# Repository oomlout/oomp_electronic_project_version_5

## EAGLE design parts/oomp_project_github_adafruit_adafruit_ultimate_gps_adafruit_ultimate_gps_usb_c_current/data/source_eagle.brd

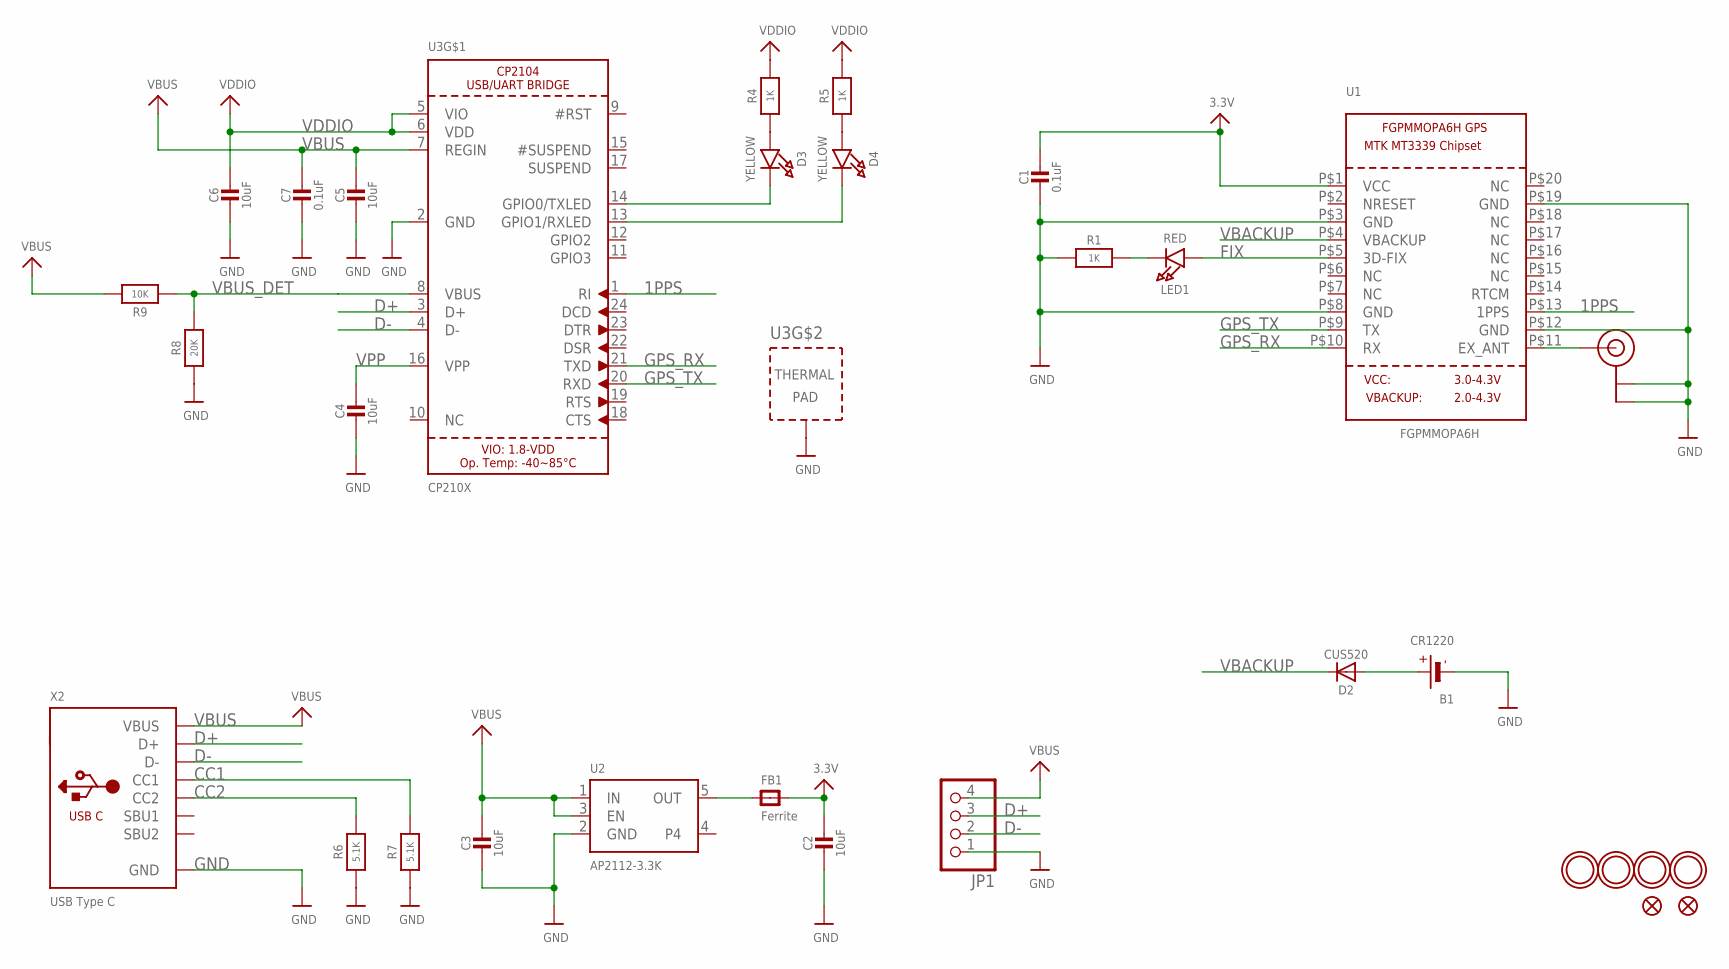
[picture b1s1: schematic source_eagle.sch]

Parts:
B1: CR1220
C1, C7: 0.1uF; 0603-NO
C2, C3, C4, C5, C6: 10uF; 0805-NO
D2: CUS520; SOD-323
D3, D4: YELLOW; CHIPLED_0805_NOOUTLINE
FB1: Ferrite; 0805-NO
FID1, FID2: FIDUCIAL_1MM
JP1: HEADER-1X4ROUND; 1X04_ROUND
LED1: RED; CHIPLED_0805_NOOUTLINE
R1, R4, R5: 1K; 0603-NO
R6, R7: 5.1K; 0603-NO
R8: 20K; 0603-NO
R9: 10K; 0603-NO
U1: FGPMMOPA6H
U2: AP2112-3.3K; SOT23-5
U3: CP210X; QFN24_4MM_SMSC
U$8, U$9, U$35, U$36: MOUNTINGHOLE2.5; MOUNTINGHOLE_2.5_PLATED
U$20: U.FL
X2: USB Type C; USB_C_CUSB31-CFM2AX-01-X

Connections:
1PPS: U1.P$13 (1PPS), U3.1 (RI)
3.3V: C1.1, C2.1, FB1.2, U1.P$1 (VCC)
CC1: R7.2, X2.A5 (CC1)
CC2: R6.2, X2.B5 (CC2)
D+: JP1.3, U3.3 (D+), X2.A6 (D+), X2.B6 (D+)
D-: JP1.2, U3.4 (D-), X2.A7 (D-), X2.B7 (D-)
FIX: LED1.A, U1.P$5 (3D-FIX)
GND: B1.-, C1.2, C2.2, C3.2, C4.2, C5.2, C6.2, C7.2, JP1.1, R1.1, R6.1, R7.1, R8.1, U1.P$3 (GND), U1.P$8 (GND), U1.P$12 (GND), U1.P$19 (GND), U2.2 (GND), U3.2 (GND), U3.THERM (TP), U$20.P$1 (GND), U$20.P$2 (GND), X2.A1B12 (GND), X2.B1A12 (GND)
GPS_RX: U1.P$10 (RX), U3.21 (TXD)
GPS_TX: U1.P$9 (TX), U3.20 (RXD)
unnamed: B1.+$1 (+), B1.+$2 (+), D2.A
unnamed: LED1.C, R1.2
unnamed: FB1.1, U2.5 (OUT)
unnamed: U1.P$11 (EX_ANT), U$20.P$3 (SIGNAL)
unnamed: D3.A, R4.1
unnamed: D4.A, R5.1
unnamed: D3.C, U3.14 (GPIO0/TXLED)
unnamed: D4.C, U3.13 (GPIO1/RXLED)
VBACKUP: D2.C, U1.P$4 (VBACKUP)
VBUS: C3.1, C5.1, C7.1, JP1.4, R9.2, U2.1 (IN), U2.3 (EN), U3.7 (REGIN), X2.A4B9 (VBUS), X2.B4A9 (VBUS)
VBUS_DET: R8.2, R9.1, U3.8 (VBUS)
VDDIO: C6.1, R4.2, R5.2, U3.5 (VIO), U3.6 (VDD)
VPP: C4.1, U3.16 (VPP)

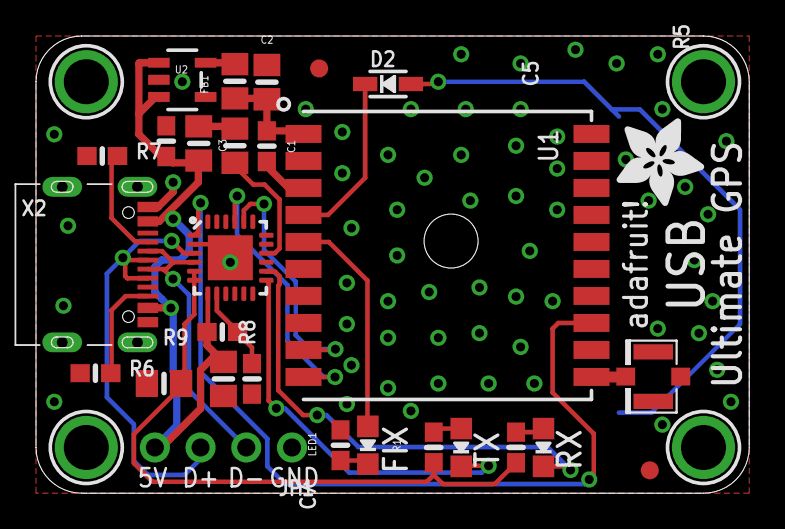
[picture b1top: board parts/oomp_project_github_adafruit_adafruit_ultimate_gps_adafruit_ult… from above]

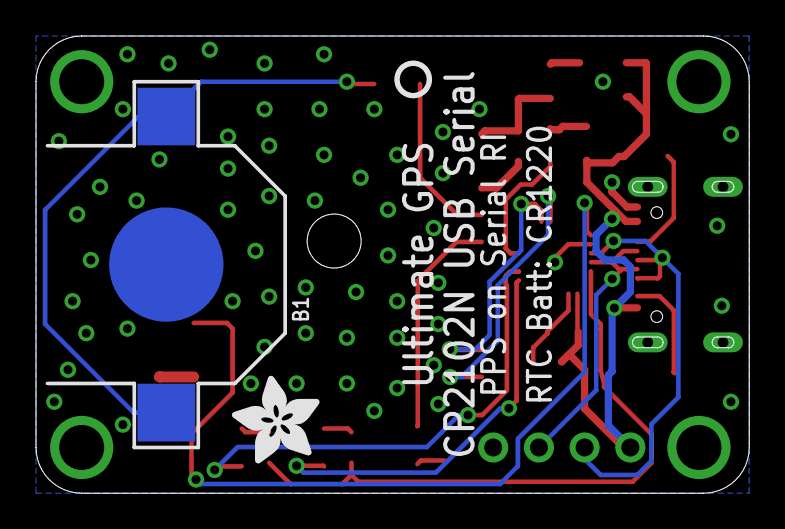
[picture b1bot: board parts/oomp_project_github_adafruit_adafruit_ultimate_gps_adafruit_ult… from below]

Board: 2 copper layers, 39.6 x 25.4 mm, 35 parts (3 on the bottom side), 23 nets.

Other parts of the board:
U$13, U$18: ADAFRUIT_5MM
U$16: PCBFEAT-REV-040

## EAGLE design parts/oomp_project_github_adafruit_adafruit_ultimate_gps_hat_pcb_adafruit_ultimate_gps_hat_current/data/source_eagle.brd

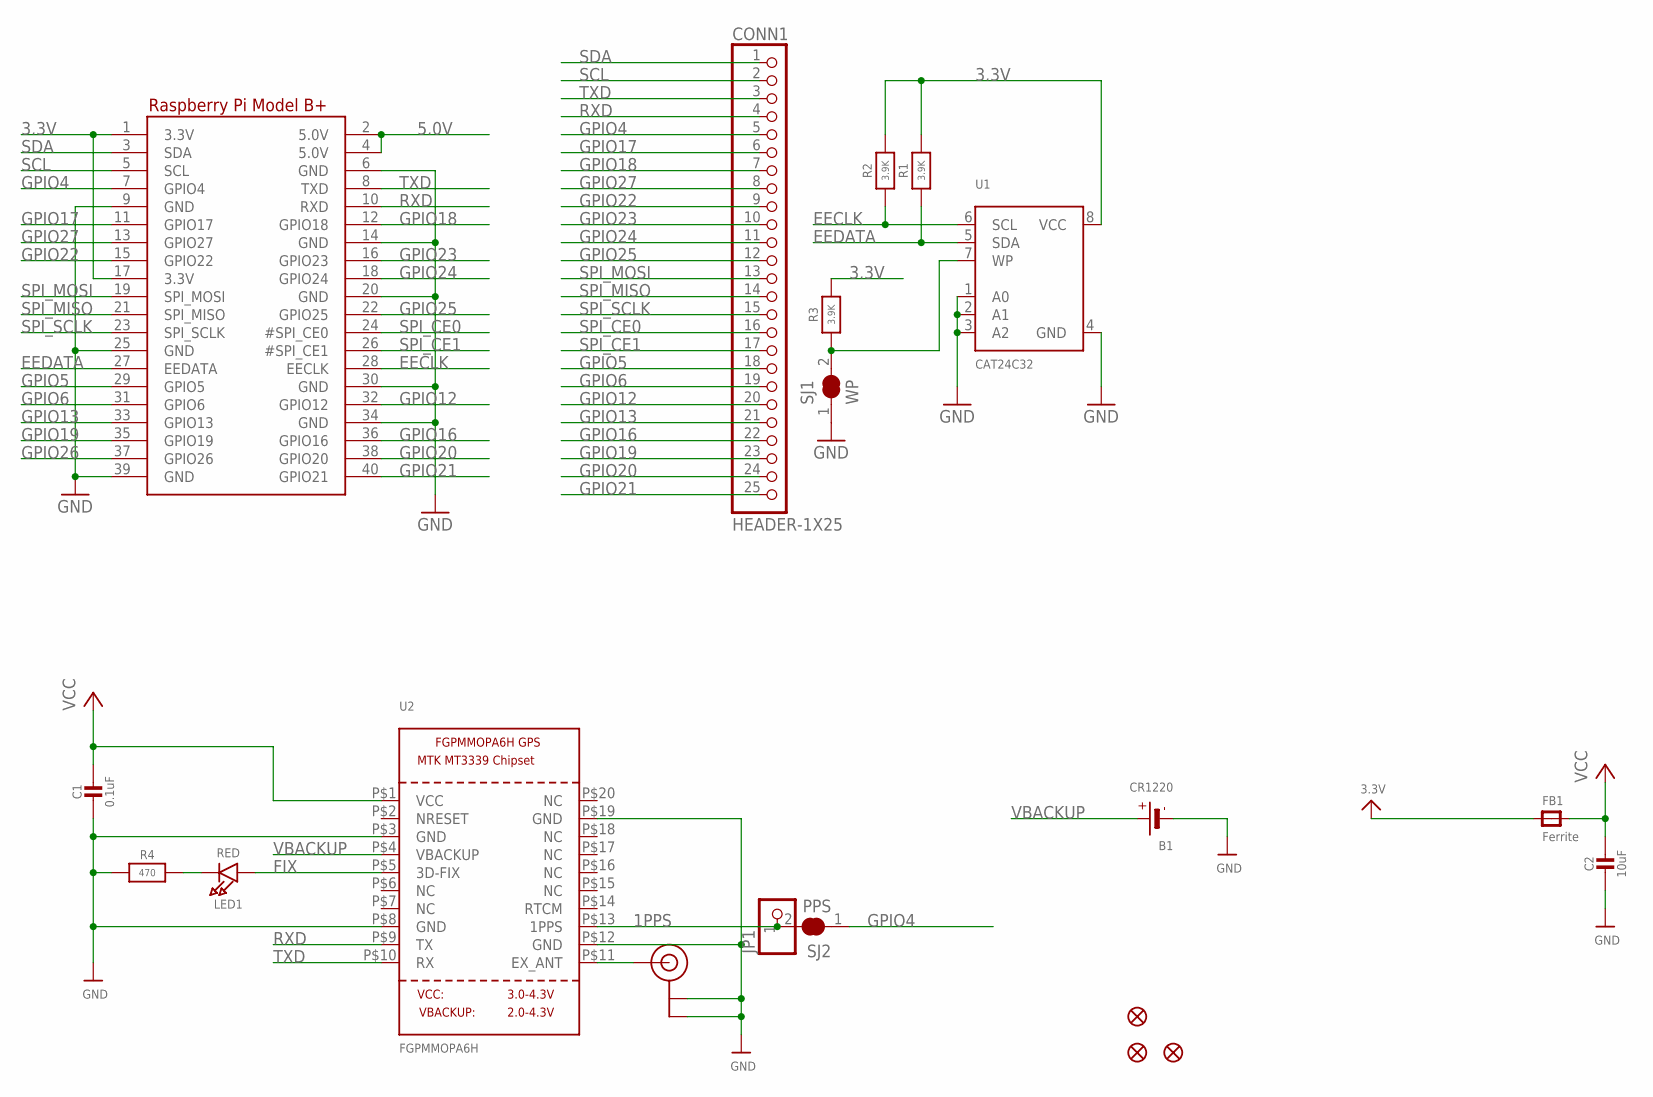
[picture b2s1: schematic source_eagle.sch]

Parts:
B1: CR1220
C1: 0.1uF; 0805-NO
C2: 10uF; 0805-NO
CONN1: HEADER-1X25; 1X25_ROUND_70MIL
FB1: Ferrite; 0805
FID1, FID2, FID3: FIDUCIAL""; FIDUCIAL_1MM
JP1: PINHD-1X1CB; 1X01-CLEANBIG
LED1: RED; CHIPLED_0805
R1, R2, R3: 3.9K; 0805-NO
R4: 470; 0805-NO
RPI1: RASPBERRYPI_BPLUS_HATSLOTS; PI_HAT_SLOTS
SJ1: WP; SOLDERJUMPER_CLOSEDWIRE
SJ2: PPS; SOLDERJUMPER_CLOSEDWIRE
U1: CAT24C32; SOIC8_150MIL
U2: FGPMMOPA6H
U$20: U.FL

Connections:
1PPS: JP1.1, SJ2.2, U2.P$13 (1PPS)
3.3V: FB1.1, R1.2, R2.2, R3.2, RPI1.1 (3.3V), RPI1.17 (3.3V), U1.8 (VCC)
5.0V: RPI1.2 (5.0V), RPI1.4 (5.0V)
EECLK: R2.1, RPI1.28 (EECLK), U1.6 (SCL)
EEDATA: R1.1, RPI1.27 (EEDATA), U1.5 (SDA)
FIX: LED1.A, U2.P$5 (3D-FIX)
GND: B1.-, C1.2, C2.2, R4.1, RPI1.6 (GND), RPI1.9 (GND), RPI1.14 (GND), RPI1.20 (GND), RPI1.25 (GND), RPI1.30 (GND), RPI1.34 (GND), RPI1.39 (GND), SJ1.1, U1.1 (A0), U1.2 (A1), U1.3 (A2), U1.4 (GND), U2.P$3 (GND), U2.P$8 (GND), U2.P$12 (GND), U2.P$19 (GND), U$20.P$1 (GND), U$20.P$2 (GND)
GPIO4: CONN1.5, RPI1.7 (GPIO4), SJ2.1
GPIO5: CONN1.18, RPI1.29 (GPIO5)
GPIO6: CONN1.19, RPI1.31 (GPIO6)
GPIO12: CONN1.20, RPI1.32 (GPIO12)
GPIO13: CONN1.21, RPI1.33 (GPIO13)
GPIO16: CONN1.22, RPI1.36 (GPIO16)
GPIO17: CONN1.6, RPI1.11 (GPIO17)
GPIO18: CONN1.7, RPI1.12 (GPIO18)
GPIO19: CONN1.23, RPI1.35 (GPIO19)
GPIO20: CONN1.24, RPI1.38 (GPIO20)
GPIO21: CONN1.25, RPI1.40 (GPIO21)
GPIO22: CONN1.9, RPI1.15 (GPIO22)
GPIO23: CONN1.10, RPI1.16 (GPIO23)
GPIO24: CONN1.11, RPI1.18 (GPIO24)
GPIO25: CONN1.12, RPI1.22 (GPIO25)
GPIO26: RPI1.37 (GPIO26)
GPIO27: CONN1.8, RPI1.13 (GPIO27)
unnamed: R3.1, SJ1.2, U1.7 (WP)
unnamed: LED1.C, R4.2
unnamed: U2.P$11 (EX_ANT), U$20.P$3 (SIGNAL)
RXD: CONN1.4, RPI1.10 (RXD), U2.P$9 (TX)
SCL: CONN1.2, RPI1.5 (SCL)
SDA: CONN1.1, RPI1.3 (SDA)
SPI_CE0: CONN1.16, RPI1.24 (#SPI_CE0)
SPI_CE1: CONN1.17, RPI1.26 (#SPI_CE1)
SPI_MISO: CONN1.14, RPI1.21 (SPI_MISO)
SPI_MOSI: CONN1.13, RPI1.19 (SPI_MOSI)
SPI_SCLK: CONN1.15, RPI1.23 (SPI_SCLK)
TXD: CONN1.3, RPI1.8 (TXD), U2.P$10 (RX)
VBACKUP: B1.+$1 (+), U2.P$4 (VBACKUP)
VCC: C1.1, C2.1, FB1.2, U2.P$1 (VCC)

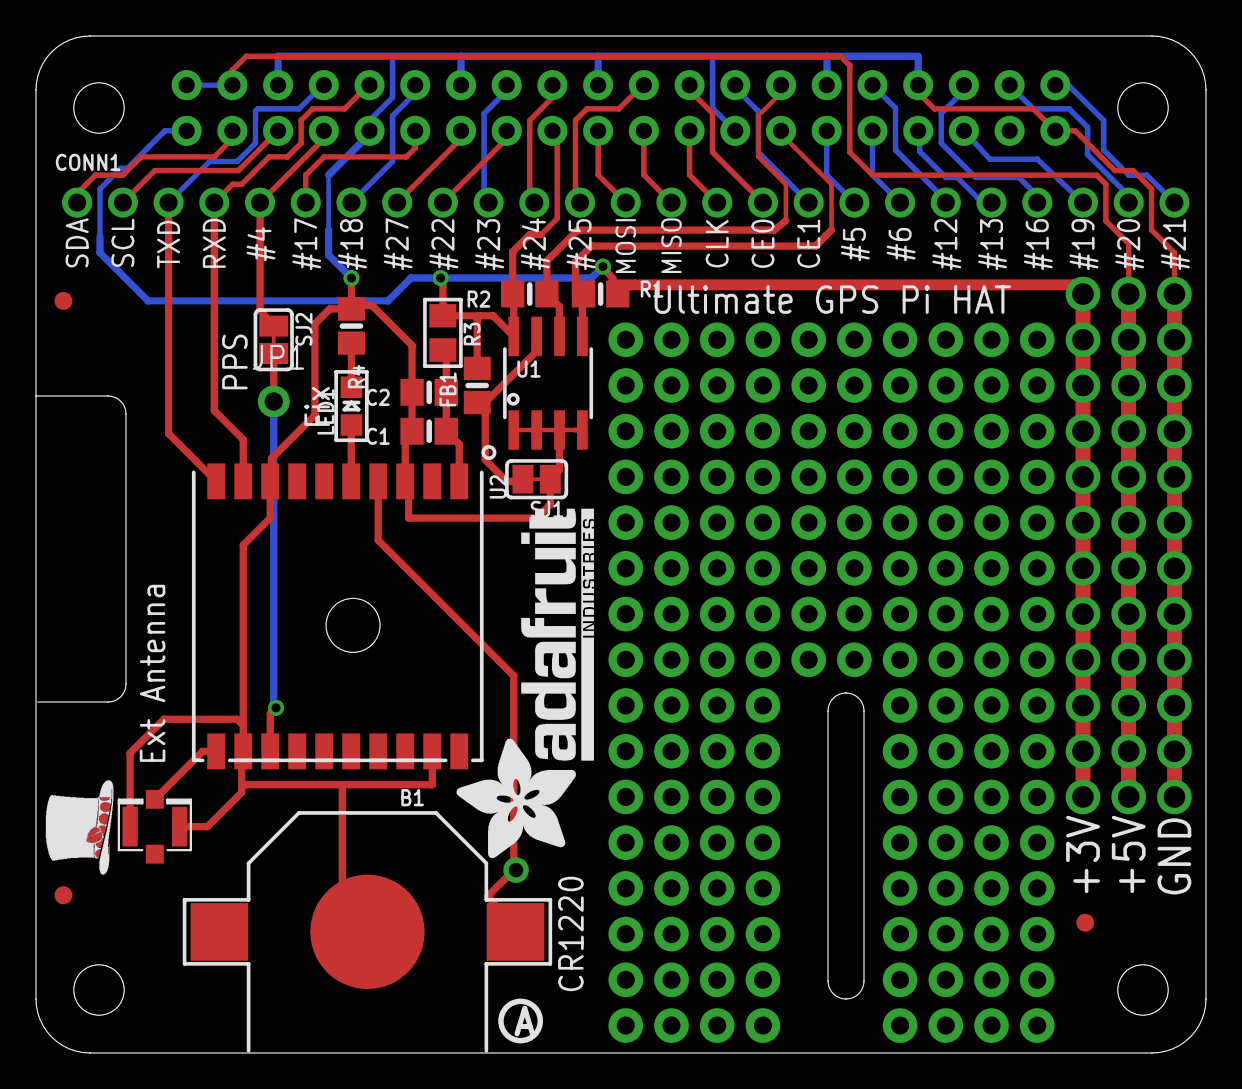
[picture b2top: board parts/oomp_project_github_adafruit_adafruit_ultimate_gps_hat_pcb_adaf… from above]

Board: 2 copper layers, 65.0 x 56.5 mm, 23 parts (0 on the bottom side), 37 nets.

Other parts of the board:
U$3: ADAFRUIT_TEXT_20MM
U$4: PIHATLOGO
U$6: PCBFEAT-REV-056

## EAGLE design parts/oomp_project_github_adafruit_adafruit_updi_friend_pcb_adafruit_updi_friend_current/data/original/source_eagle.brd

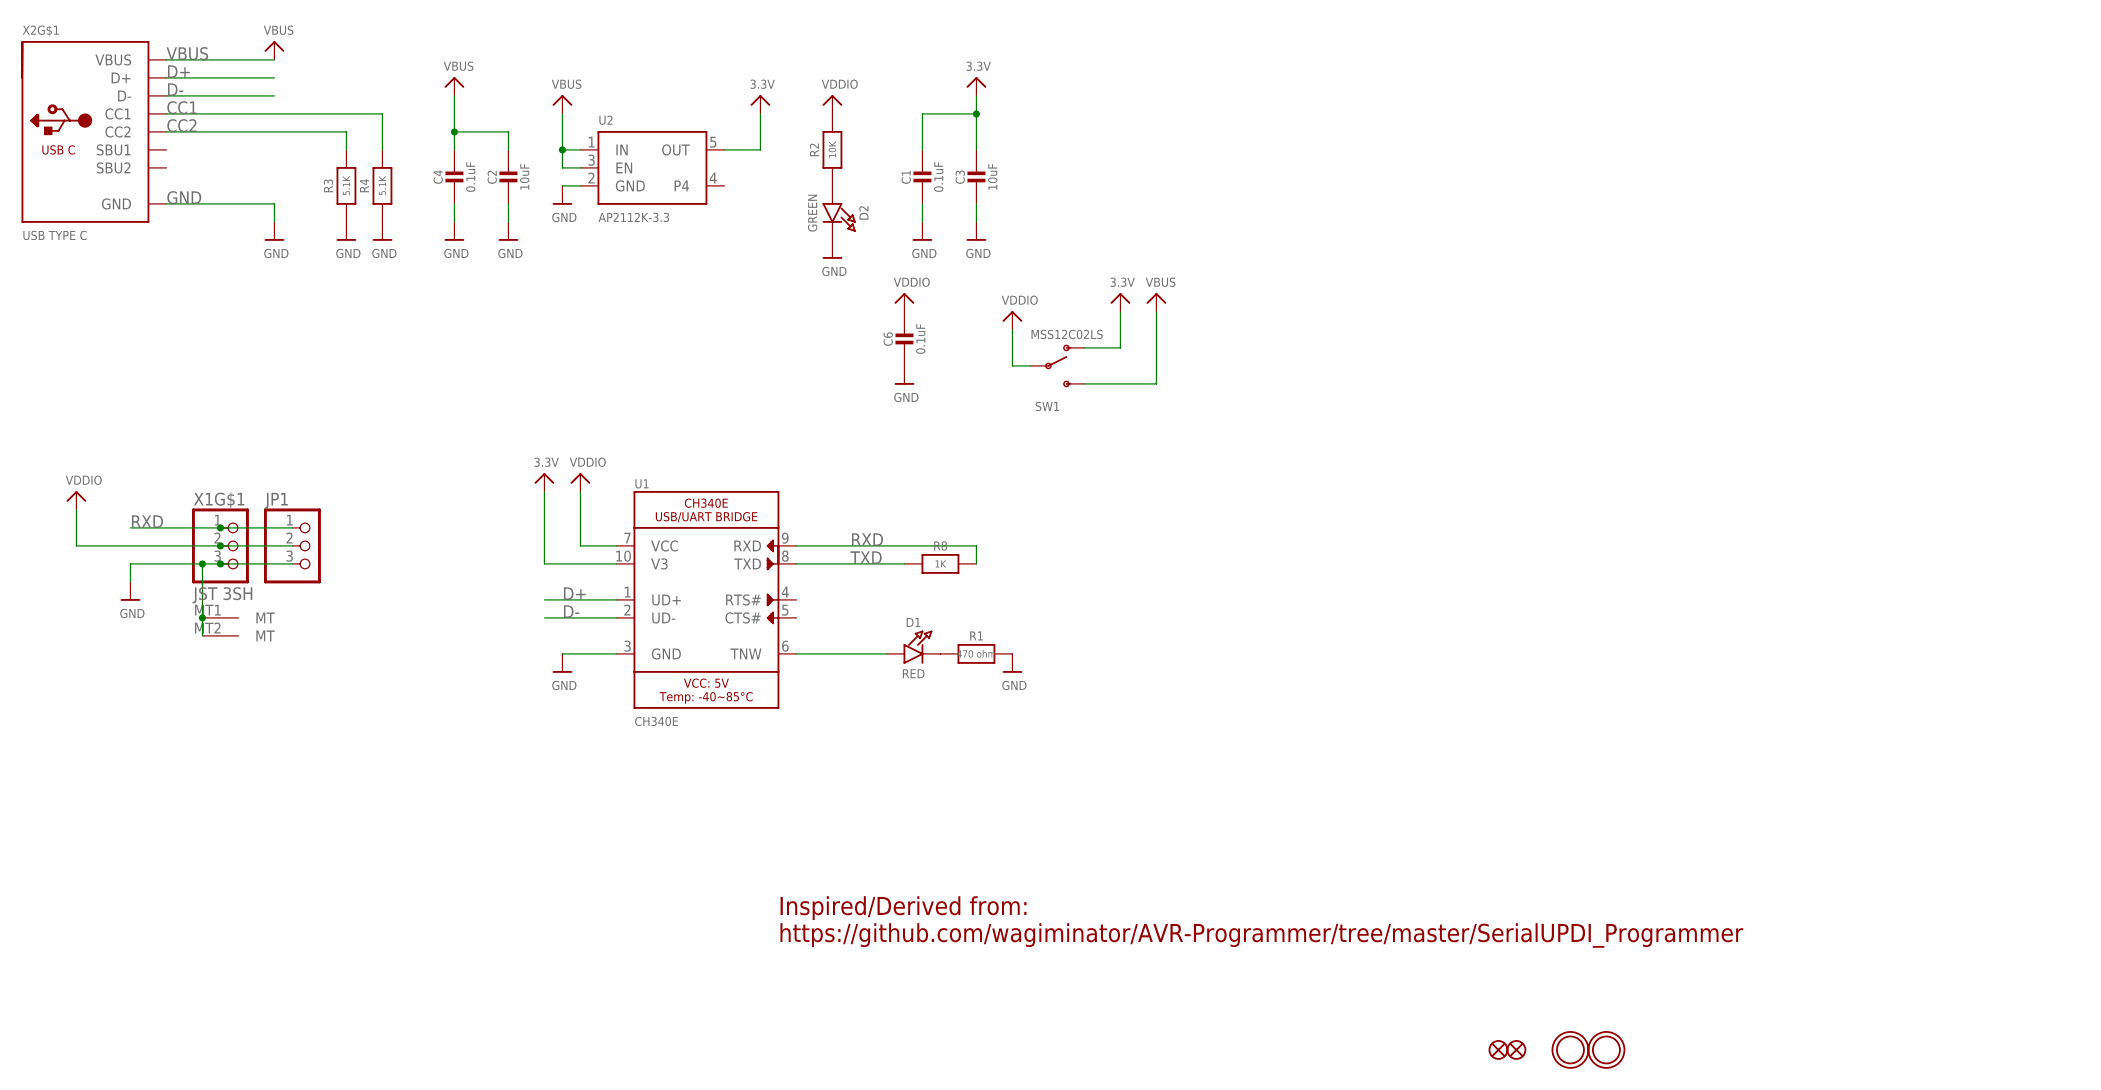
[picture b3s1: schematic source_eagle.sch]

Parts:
C1, C4, C6: 0.1uF; 0603-NO
C2, C3: 10uF; 0805-NO
D1: RED; CHIPLED_0603_NOOUTLINE
D2: GREEN; CHIPLED_0603_NOOUTLINE
FID1, FID2: FIDUCIAL_1MM
JP1: HEADER-1X376MIL; 1X03_ROUND_76
R1: 470 ohm; 0603-NO
R2: 10K; 0603-NO
R3, R4: 5.1K; 0603-NO
R8: 1K; 0603-NO
SW1: MSS12C02LS; SPDT_SMT_SSSS811101
U1: CH340E; MSOP10
U2: AP2112K-3.3; SOT23-5; JLC_ROTATION 0
U$18, U$19: MOUNTINGHOLE2.0; MOUNTINGHOLE_2.0_PLATED
X1: JST 3SH; JST_SH3
X2: USB TYPE C; USB_C_CUSB31-CFM2AX-01-X

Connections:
3.3V: C1.1, C3.1, SW1.A (O), U1.10 (V3), U2.5 (OUT)
CC1: R4.2, X2.A5 (CC1)
CC2: R3.2, X2.B5 (CC2)
D+: U1.1 (UD+), X2.A6 (D+), X2.B6 (D+)
D-: U1.2 (UD-), X2.A7 (D-), X2.B7 (D-)
GND: C1.2, C2.2, C3.2, C4.2, C6.2, D2.C, JP1.3, R1.2, R3.1, R4.1, U1.3 (GND), U2.2 (GND), X1.3, X1.MT1 (MT), X1.MT2 (MT), X2.A1B12 (GND), X2.B1A12 (GND)
unnamed: D1.C, R1.1
unnamed: D1.A, U1.6 (TNW)
unnamed: D2.A, R2.1
RXD: JP1.1, R8.2, U1.9 (RXD), X1.1
TXD: R8.1, U1.8 (TXD)
VBUS: C2.1, C4.1, SW1.C (S), U2.1 (IN), U2.3 (EN), X2.A4B9 (VBUS), X2.B4A9 (VBUS)
VDDIO: C6.1, JP1.2, R2.2, SW1.B, U1.7 (VCC), X1.2

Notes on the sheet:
Inspired/Derived from: https://github.com/wagiminator/AVR-Programmer/tree/master/SerialUPDI_Programmer

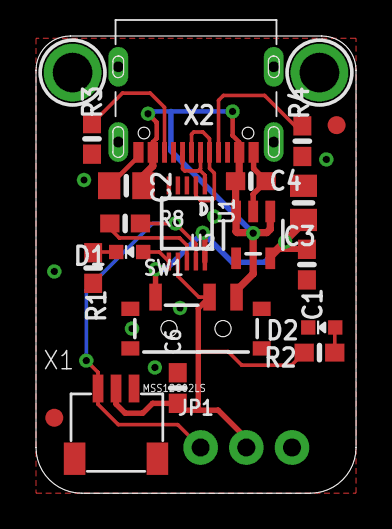
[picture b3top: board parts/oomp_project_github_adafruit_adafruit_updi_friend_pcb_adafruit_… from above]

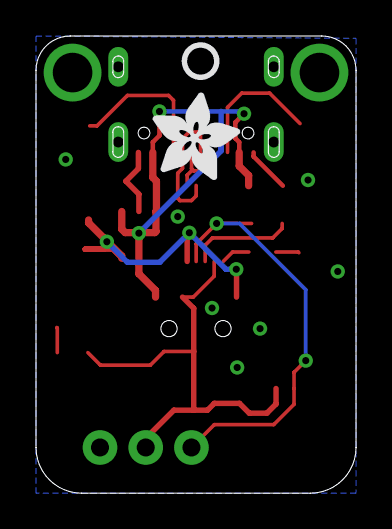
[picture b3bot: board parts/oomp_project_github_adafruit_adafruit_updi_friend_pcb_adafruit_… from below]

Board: 2 copper layers, 17.8 x 25.4 mm, 37 parts (7 on the bottom side), 13 nets.

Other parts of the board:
PLABEL0: PLABEL0
PLABEL1: PLABEL1
PLABEL2: PLABEL2
PLABEL3: PLABEL3
PLABEL4: PLABEL4
PLABEL5: PLABEL5
PLABEL6: PLABEL6
PLABEL7: PLABEL7
PLABEL8: PLABEL8
PLABEL9: PLABEL9
PLABEL10: PLABEL10
PLABEL11: PLABEL11
PLABEL12: PLABEL12
U$9: ADAFRUIT_5MM
U$17: PCBFEAT-REV-040

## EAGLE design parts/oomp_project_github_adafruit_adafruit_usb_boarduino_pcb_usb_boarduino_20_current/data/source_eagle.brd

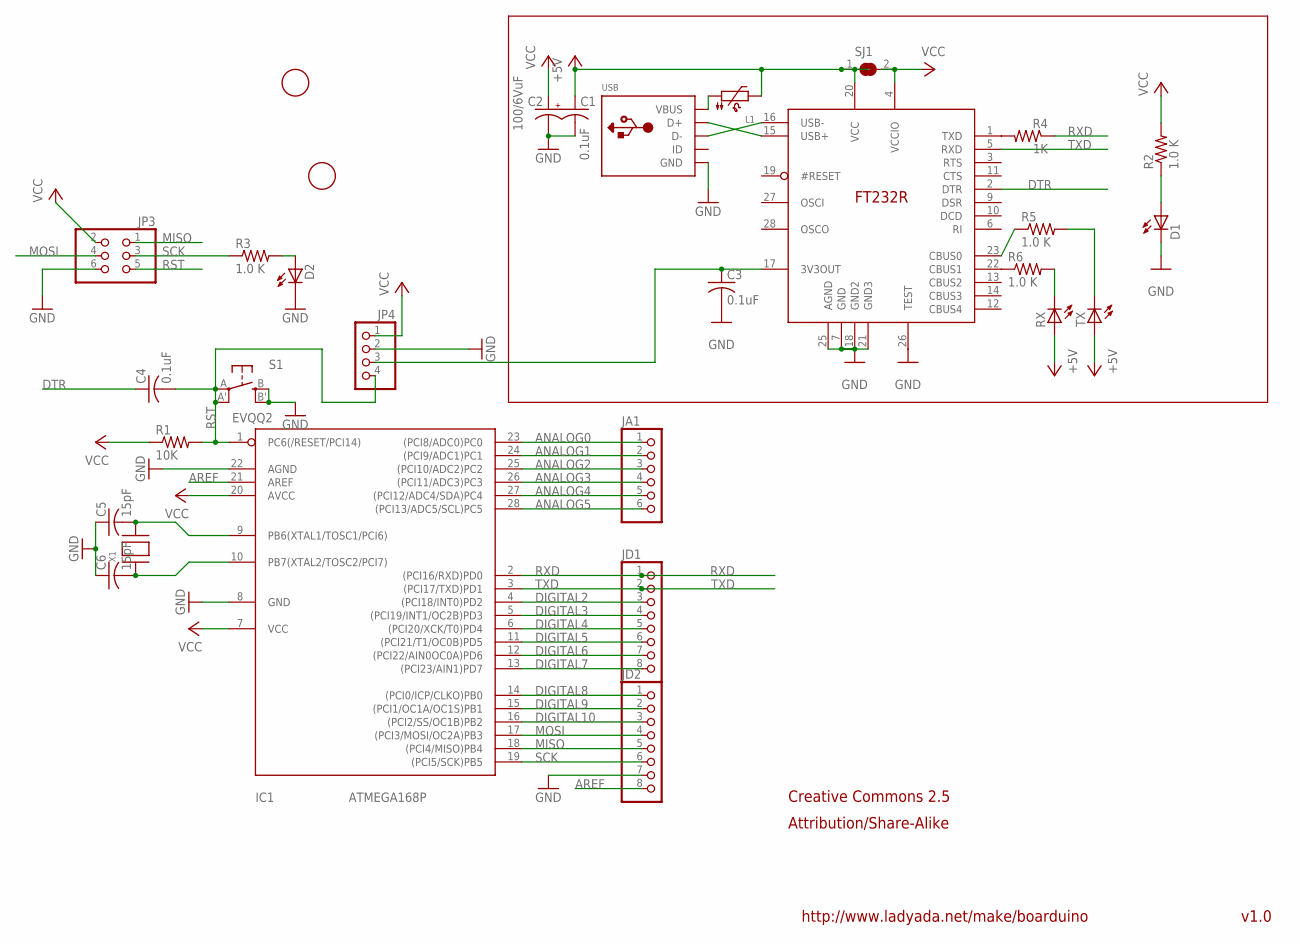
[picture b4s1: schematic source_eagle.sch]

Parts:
C1, C3, C4: 0.1uF; C0805K
C2: 100/6VuF; B/3528-21R
C5, C6: 15pF; C0805K
D1: LEDCHIPLED_0805; CHIPLED_0805
D2: Green; CHIPLED_0805
IC1: ATMEGA168P; DIL28/3
IC2: FT232R; TSSOP28
JA1: PINHD-1X6CB; 1X06-CLEANBIG
JD1, JD2: PINHD-1X8CLEANBIG; 1X08-CLEANBIG
JP3: PINHD-2X3; 2X03
JP4: PINHD-1X4CB; 1X04-CB
L1: PTC1206; 1206
R1: 10K; R0805
R2, R3, R5, R6: 1.0 K; R0805
R4: 1K; R0805
RX: Green; CHIPLED_0805
S1: EVQQ2; EVQ-Q2
SJ1: SOLDERJUMPERREFLOW; SOLDERJUMPER_REFLOW
TX: Green; CHIPLED_0805
U$1, U$2: FIDUCIAL; FIDUCIAL_1MM
USB: USBMINIB; USB-MINIB
X1: XTALNX5032; NX5032

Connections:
3V: C3.1, IC2.17 (3V3OUT), JP4.3
+5V: C1.1, IC2.20 (VCC), L1.2, RX.A, SJ1.1, TX.A
ANALOG0: IC1.23 ((PCI8/ADC0)PC0), JA1.1
ANALOG1: IC1.24 ((PCI9/ADC1)PC1), JA1.2
ANALOG2: IC1.25 ((PCI10/ADC2)PC2), JA1.3
ANALOG3: IC1.26 ((PCI11/ADC3)PC3), JA1.4
ANALOG4: IC1.27 ((PCI12/ADC4/SDA)PC4), JA1.5
ANALOG5: IC1.28 ((PCI13/ADC5/SCL)PC5), JA1.6
AREF: IC1.21 (AREF), JD2.8
DIGITAL2: IC1.4 ((PCI18/INT0)PD2), JD1.3
DIGITAL3: IC1.5 ((PCI19/INT1/OC2B)PD3), JD1.4
DIGITAL4: IC1.6 ((PCI20/XCK/T0)PD4), JD1.5
DIGITAL5: IC1.11 ((PCI21/T1/OC0B)PD5), JD1.6
DIGITAL6: IC1.12 ((PCI22/AIN0OC0A)PD6), JD1.7
DIGITAL7: IC1.13 ((PCI23/AIN1)PD7), JD1.8
DIGITAL8: IC1.14 ((PCI0/ICP/CLKO)PB0), JD2.1
DIGITAL9: IC1.15 ((PCI1/OC1A/OC1S)PB1), JD2.2
DIGITAL10: IC1.16 ((PCI2/SS/OC1B)PB2), JD2.3
DTR: C4.1, IC2.2 (DTR)
GND: C1.2, C2.-, C3.2, C5.1, C6.1, D1.C, D2.C, IC1.8 (GND), IC1.22 (AGND), IC2.7 (GND), IC2.18 (GND2), IC2.21 (GND3), IC2.25 (AGND), IC2.26 (TEST), JD2.7, JP3.6, JP4.2, S1.B (S), S1.B' (S1), USB.GND
MISO: IC1.18 ((PCI4/MISO)PB4), JD2.5, JP3.1
MOSI: IC1.17 ((PCI3/MOSI/OC2A)PB3), JD2.4, JP3.4
unnamed: C5.2, IC1.9 (PB6(XTAL1/TOSC1/PCI6)), X1.P$2
unnamed: C6.2, IC1.10 (PB7(XTAL2/TOSC2/PCI7)), X1.P$1
unnamed: D1.A, R2.1
unnamed: D2.A, R3.2
unnamed: IC2.15 (USB+), USB.D+
unnamed: IC2.16 (USB-), USB.D-
unnamed: IC2.1 (TXD), R4.2
unnamed: L1.1, USB.VBUS
unnamed: R6.2, RX.C
unnamed: R5.2, TX.C
unnamed: IC2.22 (CBUS1), R6.1
unnamed: IC2.23 (CBUS0), R5.1
RST: C4.2, IC1.1 (PC6(/RESET/PCI14)), JP3.5, JP4.4, R1.2, S1.A, S1.A' (P1)
RXD: IC1.2 ((PCI16/RXD)PD0), JD1.1, R4.1
SCK: IC1.19 ((PCI5/SCK)PB5), JD2.6, JP3.3, R3.1
TXD: IC1.3 ((PCI17/TXD)PD1), IC2.5 (RXD), JD1.2
VCC: C2.+, IC1.7 (VCC), IC1.20 (AVCC), IC2.4 (VCCIO), JP3.2, JP4.1, R1.1, R2.2, SJ1.2

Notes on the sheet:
v1.0
http://www.ladyada.net/make/boarduino
Creative Commons 2.5
Attribution/Share-Alike

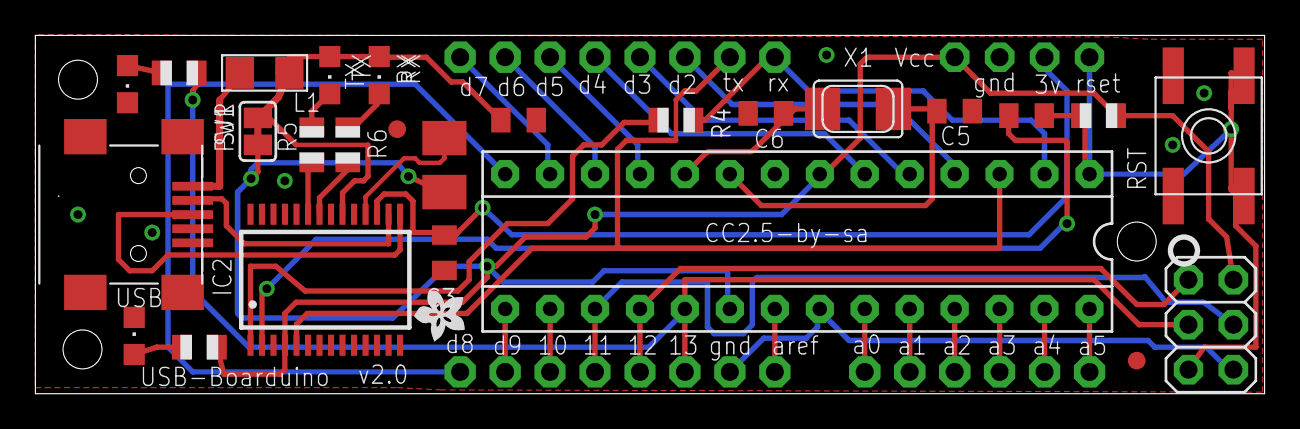
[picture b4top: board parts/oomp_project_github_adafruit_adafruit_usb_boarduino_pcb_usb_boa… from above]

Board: 2 copper layers, 69.4 x 20.2 mm, 31 parts (0 on the bottom side), 39 nets.

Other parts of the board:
U$3: ADAFRUIT200MIL

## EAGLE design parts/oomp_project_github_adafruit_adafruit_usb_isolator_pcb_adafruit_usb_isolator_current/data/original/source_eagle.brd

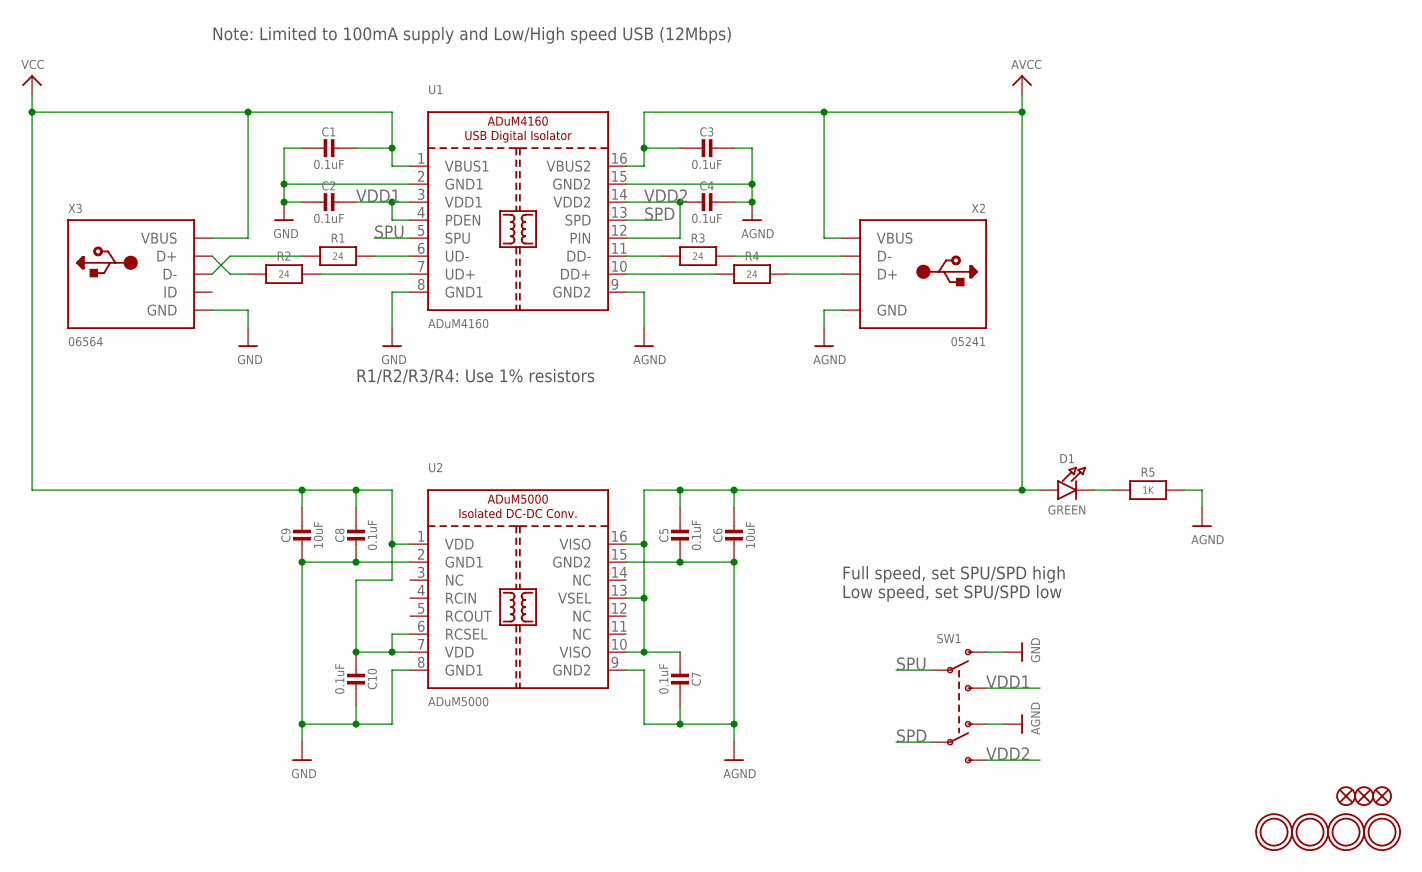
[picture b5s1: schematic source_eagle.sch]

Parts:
C1, C2, C3, C4, C5, C7, C8, C10: 0.1uF; 0805-NO
C6, C9: 10uF; 0805-NO
D1: GREEN; CHIPLED_0805_NOOUTLINE
FID1, FID2, FID3: FIDUCIAL""; FIDUCIAL_1MM
R1, R2, R3: 24; 0805-NO
R4: 24; _0805MP
R5: 1K; 0805-NO
SW1: SWITCH_DPDTEG1390; EG1390
U1: ADuM4160; SOIC16WIDE
U2: ADuM5000; SOIC16WIDE
U$7, U$8, U$9, U$10: MOUNTINGHOLE2.5_THICK; MOUNTINGHOLE_2.5_PLATED_THICK
X2: 05241; USB_HOST-PTH
X3: 06564; USB-MINIB_LARGER

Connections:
AGND: C3.1, C4.1, C5.2, C6.2, C7.1, R5.2, SW1.O2, U1.9 (GND2), U1.15 (GND2), U2.9 (GND2), U2.15 (GND2), X2.GND
AVCC: C3.2, C5.1, C6.1, C7.2, D1.A, U1.16 (VBUS2), U2.10 (VISO), U2.13 (VSEL), U2.16 (VISO), X2.VBUS
GND: C1.2, C2.2, C8.2, C9.2, C10.1, SW1.O1, U1.2 (GND1), U1.8 (GND1), U2.2 (GND1), U2.8 (GND1), X3.GND, X3.GND1 (GND), X3.GND2 (GND), X3.GND3 (GND), X3.GND4 (GND)
unnamed: R2.1, X3.D+
unnamed: R2.2, U1.7 (UD+)
unnamed: R1.2, U1.6 (UD-)
unnamed: R1.1, X3.D-
unnamed: R4.1, U1.10 (DD+)
unnamed: R4.2, X2.D+
unnamed: R3.2, X2.D-
unnamed: R3.1, U1.11 (DD-)
unnamed: D1.C, R5.1
SPD: SW1.P2, U1.13 (SPD)
SPU: SW1.P1, U1.5 (SPU)
VCC: C1.1, C8.1, C9.1, C10.2, U1.1 (VBUS1), U2.1 (VDD), U2.6 (RCSEL), U2.7 (VDD), X3.VBUS
VDD1: C2.1, SW1.S1, U1.3 (VDD1), U1.4 (PDEN)
VDD2: C4.2, SW1.S2, U1.12 (PIN), U1.14 (VDD2)

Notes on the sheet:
R1/R2/R3/R4: Use 1% resistors
Note: Limited to 100mA supply and Low/High speed USB (12Mbps)
Full speed, set SPU/SPD high Low speed, set SPU/SPD low

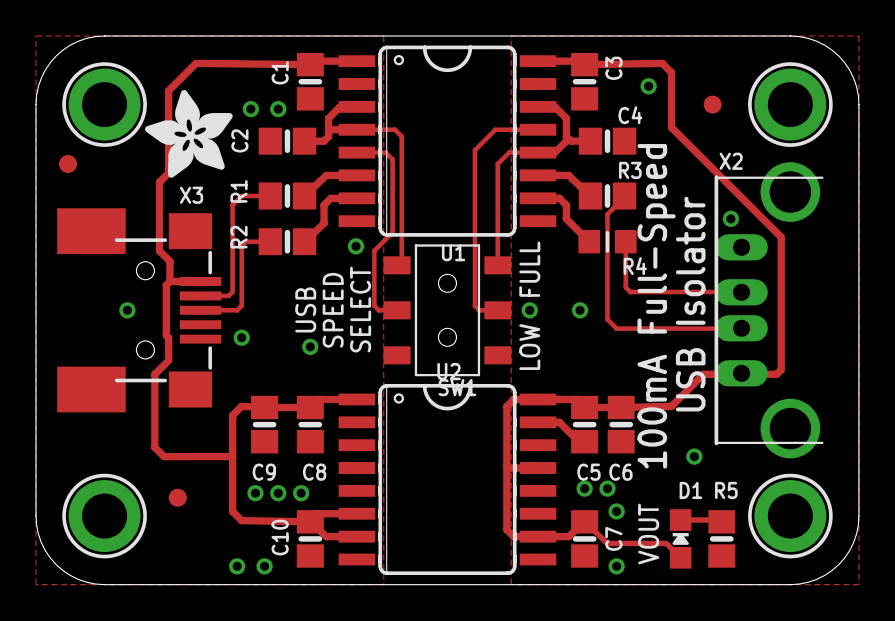
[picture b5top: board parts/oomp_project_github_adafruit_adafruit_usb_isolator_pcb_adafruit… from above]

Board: 2 copper layers, 45.7 x 30.5 mm, 30 parts (1 on the bottom side), 17 nets.

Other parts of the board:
U$14: ADAFRUIT_5MM
U$16: ADAFRUIT_TEXT_30MM

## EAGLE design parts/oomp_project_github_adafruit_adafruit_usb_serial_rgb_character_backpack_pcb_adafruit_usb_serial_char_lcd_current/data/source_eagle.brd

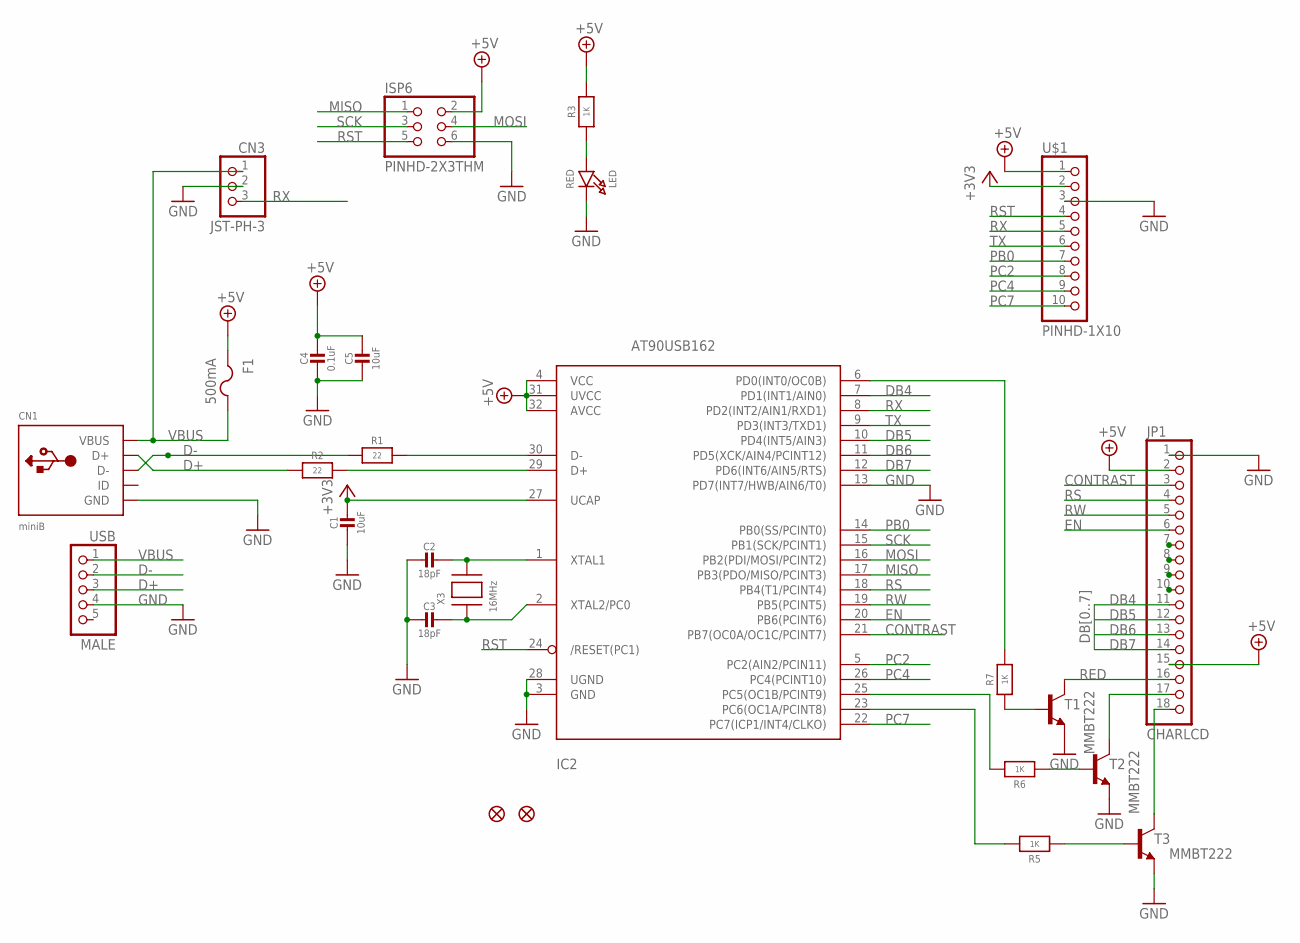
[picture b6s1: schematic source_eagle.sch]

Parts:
C1, C5: 10uF; 0805-NO
C2, C3: 18pF; 0805-NO
C4: 0.1uF; 0805-NO
CN1: miniB; USB-MINIB_LARGER
CN3: JST-PH-3; JSTPH3
F1: 500mA; R1206
FID1, FID2: FIDUCIAL1X2.5; FIDUCIAL-1X2.5
IC2: AT90USB162; TQFP32-08
ISP6: PINHD-2X3THM; ISP6
JP1: CHARLCD; 1X18-BIG
LED: RED; CHIPLED_0805_NOOUTLINE
R1, R2: 22; 0805-NO
R3, R5, R6, R7: 1K; 0805-NO
T1, T2, T3: MMBT222; SOT23-BEC
U$1: PINHD-1X10; 1X10-BIG
USB: MALE; 1X05
X3: 16MHz; NX5032

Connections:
+3V3: C1.1, IC2.27 (UCAP), U$1.2
+5V: C4.1, C5.1, F1.1, IC2.4 (VCC), IC2.31 (UVCC), IC2.32 (AVCC), ISP6.2, JP1.2, JP1.15, R3.2, U$1.1
BLUE: JP1.18, T3.C
CONTRAST: IC2.21 (PB7(OC0A/OC1C/PCINT7)), JP1.3
D+: CN1.D+, R2.1, USB.3
D-: CN1.D-, R1.1, USB.2
DB0: JP1.7
DB1: JP1.8
DB2: JP1.9
DB3: JP1.10
DB4: IC2.7 (PD1(INT1/AIN0)), JP1.11
DB5: IC2.10 (PD4(INT5/AIN3)), JP1.12
DB6: IC2.11 (PD5(XCK/AIN4/PCINT12)), JP1.13
DB7: IC2.12 (PD6(INT6/AIN5/RTS)), JP1.14
EN: IC2.20 (PB6(PCINT6)), JP1.6
GND: C1.2, C2.2, C3.2, C4.2, C5.2, CN1.GND, CN3.2, IC2.3 (GND), IC2.13 (PD7(INT7/HWB/AIN6/T0)), IC2.28 (UGND), ISP6.6, JP1.1, LED.C, T1.E, T2.E, T3.E, U$1.3, USB.4
GREEN: JP1.17, T2.C
MISO: IC2.17 (PB3(PDO/MISO/PCINT3)), ISP6.1
MOSI: IC2.16 (PB2(PDI/MOSI/PCINT2)), ISP6.4
unnamed: LED.A, R3.1
unnamed: R7.1, T1.B
unnamed: IC2.30 (D-), R1.2
unnamed: IC2.29 (D+), R2.2
unnamed: IC2.6 (PD0(INT0/OC0B)), R7.2
unnamed: R6.1, T2.B
unnamed: IC2.25 (PC5(OC1B/PCINT9)), R6.2
unnamed: C2.1, IC2.1 (XTAL1), X3.P$2
unnamed: C3.1, IC2.2 (XTAL2/PC0), X3.P$1
unnamed: IC2.23 (PC6(OC1A/PCINT8)), R5.2
unnamed: R5.1, T3.B
PB0: IC2.14 (PB0(SS/PCINT0)), U$1.7
PC2: IC2.5 (PC2(AIN2/PCIN11)), U$1.8
PC4: IC2.26 (PC4(PCINT10)), U$1.9
PC7: IC2.22 (PC7(ICP1/INT4/CLKO)), U$1.10
RED: JP1.16, T1.C
RS: IC2.18 (PB4(T1/PCINT4)), JP1.4
RST: IC2.24 (/RESET(PC1)), ISP6.5, U$1.4
RW: IC2.19 (PB5(PCINT5)), JP1.5
RX: CN3.3, IC2.8 (PD2(INT2/AIN1/RXD1)), U$1.5
SCK: IC2.15 (PB1(SCK/PCINT1)), ISP6.3
TX: IC2.9 (PD3(INT3/TXD1)), U$1.6
VBUS: CN1.VBUS, CN3.1, F1.2, USB.1

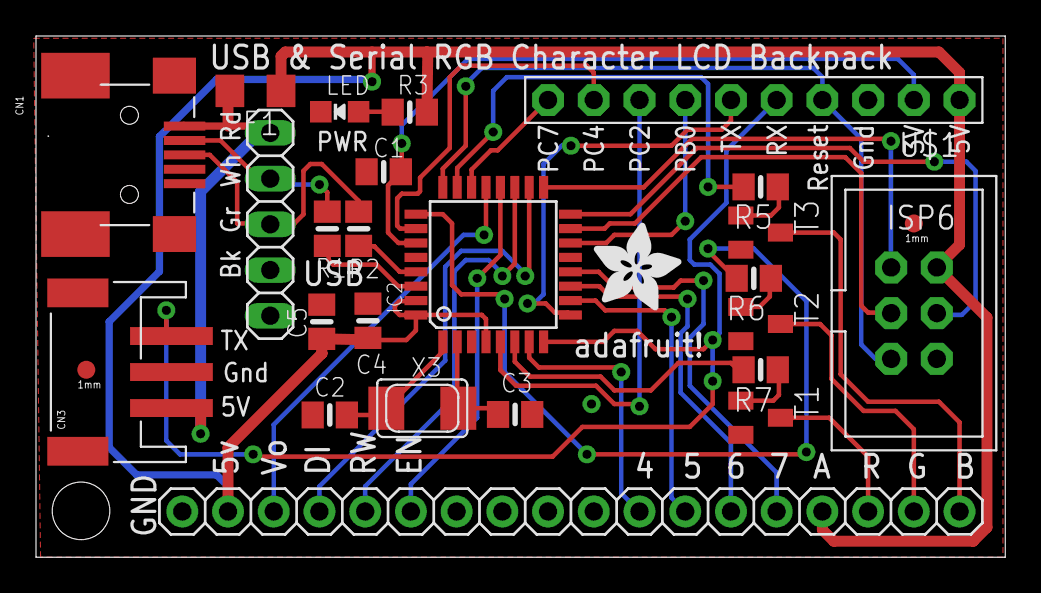
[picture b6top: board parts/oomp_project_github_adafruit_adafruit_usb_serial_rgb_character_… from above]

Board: 2 copper layers, 53.8 x 29.0 mm, 27 parts (0 on the bottom side), 38 nets.

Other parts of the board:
U$2: ADAFRUIT_5MM

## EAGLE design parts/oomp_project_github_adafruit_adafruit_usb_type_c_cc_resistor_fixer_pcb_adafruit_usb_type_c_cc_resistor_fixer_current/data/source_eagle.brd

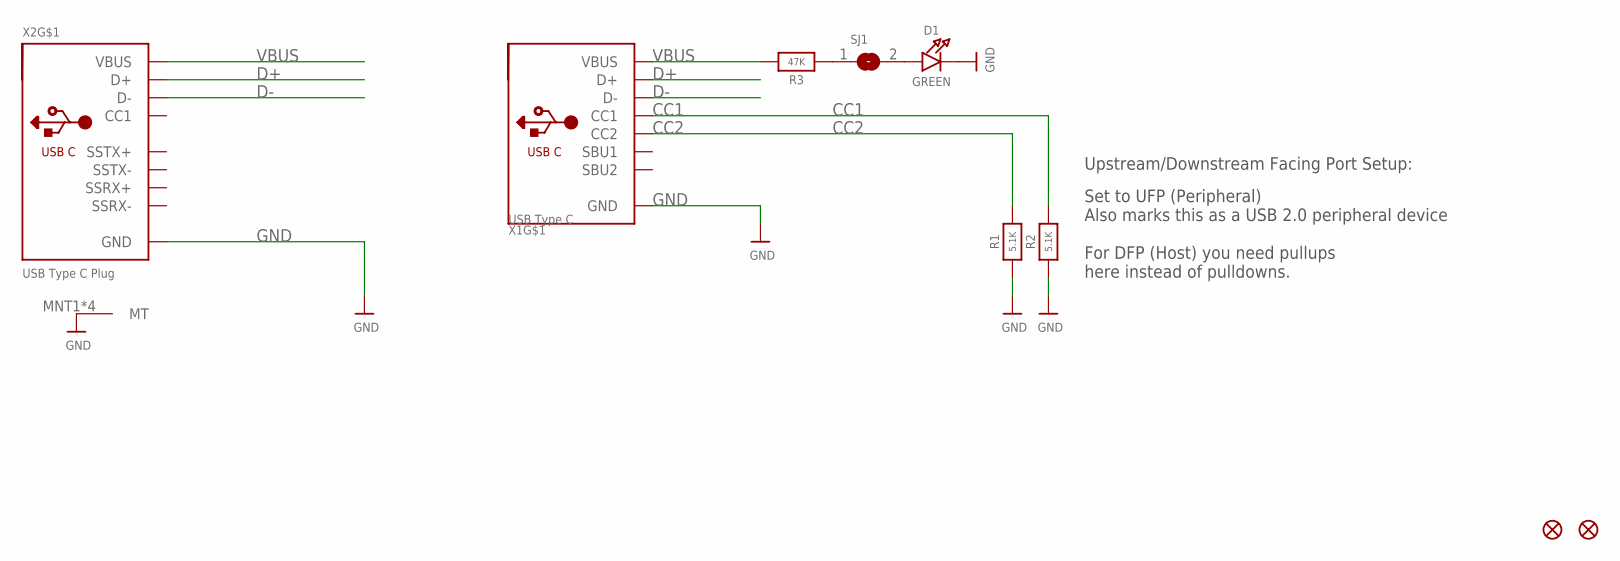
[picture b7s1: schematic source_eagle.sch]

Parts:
D1: GREEN; CHIPLED_0603_NOOUTLINE
FID1, FID2: FIDUCIAL_0.5MM
R1, R2: 5.1K; 0603-NO
R3: 47K; 0603-NO
SJ1: SOLDERJUMPERCLOSED; SOLDERJUMPER_CLOSEDWIRE
X1: USB Type C; USB_C_SINK
X2: USB Type C Plug; USB_TYPEC_PLUG_12P

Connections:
CC1: R2.2, X1.A5 (CC1)
CC2: R1.2, X1.B5 (CC2)
D+: X1.A6 (D+), X1.B6 (D+), X2.A6 (D+)
D-: X1.A7 (D-), X1.B7 (D-), X2.A7 (D-)
GND: D1.C, R1.1, R2.1, X1.A1B12 (GND), X1.B1A12 (GND), X2.A1 (GND), X2.A12 (GND), X2.B12 (GND), X2.MNT1 (MT), X2.MNT2 (MT), X2.P$1 (MT), X2.P$2 (MT)
unnamed: R3.1, SJ1.1
unnamed: D1.A, SJ1.2
VBUS: R3.2, X1.A4B9 (VBUS), X1.B4A9 (VBUS), X2.A4 (VBUS), X2.B9 (VBUS)

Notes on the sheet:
Set to UFP (Peripheral) Also marks this as a USB 2.0 peripheral device For DFP (Host) you need pullups here instead of pulldowns.
Upstream/Downstream Facing Port Setup:

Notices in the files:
parts and their libraries:
microbuilder: This work is placed in the public domain, and may be freely used for commercial and non-commercial work with the following conditions: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
